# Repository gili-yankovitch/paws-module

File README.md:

# paws-module
ATTiny85 Smart Key Switch Module

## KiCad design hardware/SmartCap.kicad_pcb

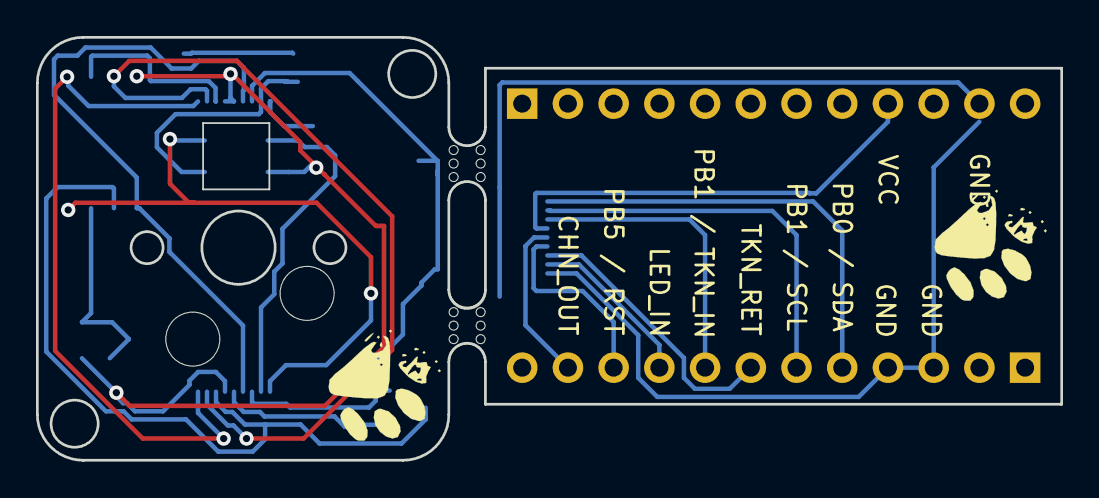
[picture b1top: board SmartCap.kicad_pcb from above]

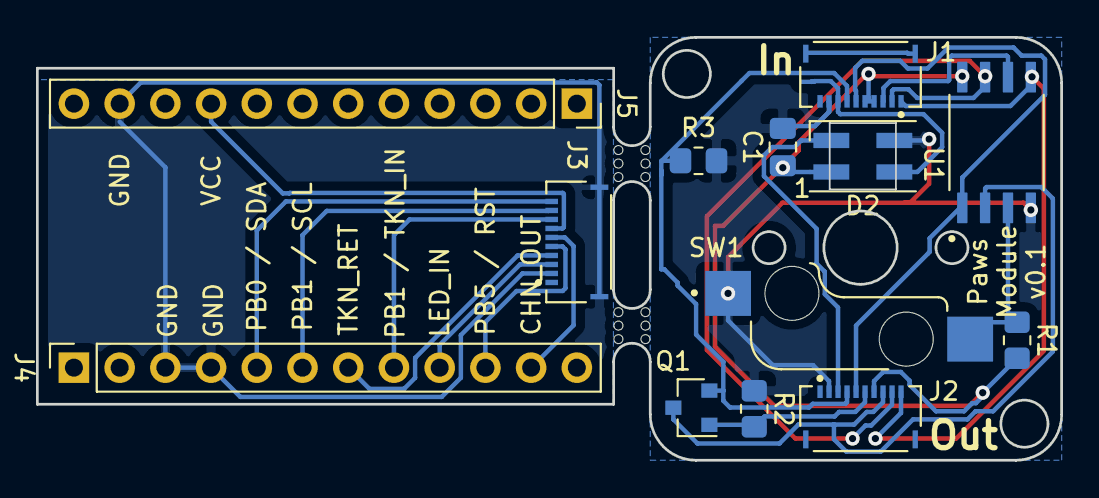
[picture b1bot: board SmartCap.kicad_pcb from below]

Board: 2 copper layers, 56.9 x 23.5 mm, 15 parts (13 on the bottom side), 23 nets.

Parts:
C1: 0.1uF; C_0805_2012Metric_Pad1.18x1.45mm_HandSolder
D2: SK6812MINI; LED_SK6812MINI_PLCC4_3.5x3.5mm_P1.75mm
J1, J2, J3: 5034801000; MOLEX_5034801000
J4, J5: Conn_01x12_Female; PinSocket_1x12_P2.54mm_Vertical
Q1: Q_PNP_BCE; SOT-23
R1, R2, R3: 1K; R_0805_2012Metric_Pad1.20x1.40mm_HandSolder
SW1: SW_Push; SW_PG151101S11
U1: ATtiny85-20SU; SOIC127P798X216-8N
mouse-bite-2mm-slot, mouse-bite-2mm-slot#2: VAL**; mouse-bite-2mm-slot

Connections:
BREAKOUT_CHAIN_OUT: J3.6, J4.11
BREAKOUT_GND: J3.2, J3.S1, J3.S2, J4.3, J4.4, J5.11
BREAKOUT_LED_IN: J3.3, J4.9
BREAKOUT_RST: J3.5, J4.10
BREAKOUT_SCL: J3.9, J4.6
BREAKOUT_SDA: J3.10, J4.5
BREAKOUT_TOKEN_IN: J3.8, J4.8
BREAKOUT_TOKEN_RET: J3.4, J4.7
BREAKOUT_VCC: J3.7, J5.9
BTN_IN: R1.1, SW1.2, U1.3
CHAIN_IN: J2.6, Q1.1, R2.2
GND: C1.2, D2.2, J1.9, J2.2, R2.1, R3.1, SW1.1, U1.4
LED_IN: D2.1, J1.8
LED_OUT: D2.3, J2.3
unnamed: J1.S1, J1.S2
unnamed: J2.S1, J2.S2
RST: J1.6, J2.5, U1.1
SCL: J1.2, J2.9, U1.7
SDA: J1.1, J2.10, U1.5
TOKEN_IN: J1.3, U1.6
TOKEN_OUT: J2.8, Q1.3, U1.2
TOKEN_RET: J1.7, J2.4, Q1.2, R3.2
VCC: C1.1, D2.4, J1.4, J1.5, J2.7, R1.2, U1.8

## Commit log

2022-03-14 Initial commit - stable I2C communication with main module
2022-03-14 Adding TinyWire to repo - essential ATTiny I2C implementation
2022-04-03 Adding hadware schematics and BOM
2022-04-06 Changing module to master mode for push updates instead of polling
2022-04-06 Adding TinyI2CMaster to source control
2022-04-06 Fixing address provisioning race and retransmitting press to make sure it is caught
2022-04-06 TinyWireS code style changes according to VSCode
